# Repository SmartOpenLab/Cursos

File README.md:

# Cursos

Cursos impartidos por Smart Open Lab:

- Charla para laboratorios de la [Red Circular Fab](www.circular.es): *¿Qué se puede hacer en un fablab? Ejemplos desde SOL.*
  
- Curso de Arduino Básico: Entradas y salidas, Analógicas y Digitales y PWM
  
- Curso de Arduino Básico: Multi Sensor Shield

- Curso de Electrónica Básica: conceptos, dispositivos y circuitos fundamentales.
 
- Curso de Electrónica de Válvulas de Vacío para Guitarritas: Conceptos fundamentales, circuitos típicos, precauciones de seguridad...

- Curso de Freecad Básico: ejemplos de diseño y enlace a los videos del curso.

- Curso de diseño electrónico con Kicad de dos sesiones para la Red Circular Fab: ejemplos de diseño y enlace a los videos 3#.

 # Charlas

 Charlas impartidas por Smart Open Lab:
 
- Presentación de la charla impartida en "Fab17: Bali Fab Fest – Designing Emergent Realities" en Bali, Indonesia, octubre de 2022.
  
- Presentación del trabajo presentado en "FabFest 23 – Designing Relisient Futures" en Thimphu, Bután, julio de 2023.
  
- Presentación de la charla pronunciada en "FabFest 23 – Designing Relisient Futures" en Thimphu, Bután, julio de 2023.

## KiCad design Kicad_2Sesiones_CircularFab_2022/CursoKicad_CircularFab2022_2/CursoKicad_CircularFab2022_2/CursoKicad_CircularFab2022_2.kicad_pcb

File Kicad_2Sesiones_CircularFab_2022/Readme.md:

Curso de diseño electrónico con Kicad
=======

Aprende Kicad en dos sesiones online: del esquema a la PCB.

Impartidos desde el fablab [Smart Open Lab](www.smartopenlab.com), dentro del ciclo de cursos de 2022 para la dinamización de la [Red Circular Fab](https://circularfab.es/).

Contenidos
------------

**Primera sesión:** _Arrancando con Kicad_

* ¿Qué es diseño electrónico? Flujo de desarrollo de diseño.
* ¿Qué ofrece Kicad?
* ¡Manos a la obra!
* Iniciando un proyecto.
  * El editor de esquemas.
  * El editor de PCB.
  * El editor de Símbolos.
  * El editor de Huellas.

**Segunda sesión:** _Kicad intermedio_

* Campos extras en componentes.
* Añadiendo pads y agujeros.
* Añadiendo imágenes a la placa.
* Exportando modelos 3D a Freecad.
* Subiendo proyectos a webs de fabricantes (Aisler).
* Simulaciones de circuitos con Spice (link y link).

**Materiales incluídos:**
* Presentación del curso (breve).
* Enlaces a videos de youtube:
  * [Primera Sesión](https://www.youtube.com/watch?v=K_PexNjK7Dc&t=83s).
  * [Segunda Sesión](https://www.youtube.com/watch?v=kZ3RvHSpxto).
* Ficheros de diseño de los circuitos de cada sesión.
* Modelo de SPICE del transistor BC546.

**Profesor:**

[Antonio Gordillo Guerrero ](https://www.linkedin.com/in/antonio-gordillo-guerrero-8b820b88/?originalSubdomain=es) (anto@unex.es)

Departamento de Ingeniería Eléctrica Electrónica y Automática.

[Escuela Politécnica](https://www.unex.es/conoce-la-uex/centros/epcc), [Universidad de Extremadura](https://www.unex.es). España.

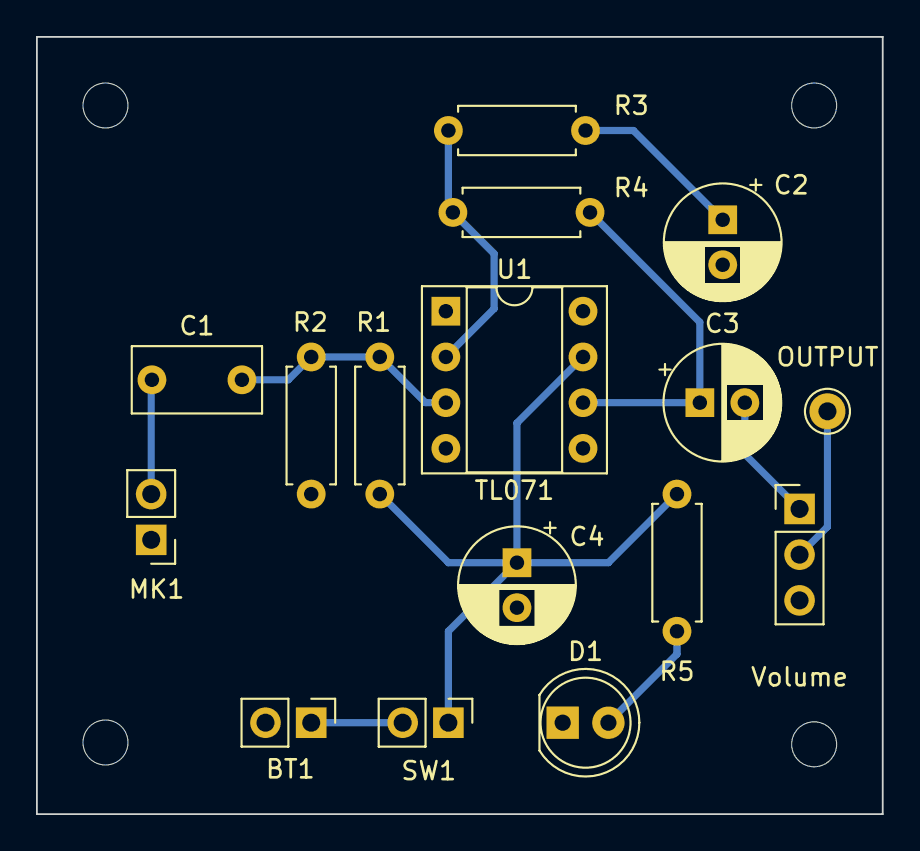
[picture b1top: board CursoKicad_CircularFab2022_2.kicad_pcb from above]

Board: 2 copper layers, 47.0 x 43.2 mm, 20 parts (0 on the bottom side), 11 nets.

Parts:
BT1: 9V; PinHeader_1x02_P2.54mm_Vertical
C1: C; C_Rect_L7.0mm_W3.5mm_P5.00mm
C2: C_Polarized; CP_Radial_D6.3mm_P2.50mm
C3, C4: 10u; CP_Radial_D6.3mm_P2.50mm
D1: Red; LED_D5.0mm
H1, H2, H3, H4: MountingHole; MountingHole_2.5mm
J1: Conn_01x01_Female; Pin_D1.0mm_L10.0mm
MK1: Piezoelectric_cell; PinHeader_1x02_P2.54mm_Vertical
R1, R2: 2M2; R_Axial_DIN0207_L6.3mm_D2.5mm_P7.62mm_Horizontal
R3: 100k; R_Axial_DIN0207_L6.3mm_D2.5mm_P7.62mm_Horizontal
R4: 220k; R_Axial_DIN0207_L6.3mm_D2.5mm_P7.62mm_Horizontal
R5: 1k; R_Axial_DIN0207_L6.3mm_D2.5mm_P7.62mm_Horizontal
RV1: R_Potentiometer; PinHeader_1x03_P2.54mm_Vertical
SW1: Switch_SPST; PinHeader_1x02_P2.54mm_Vertical
U1: TL071; DIP-8_W7.62mm_Socket

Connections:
GND: BT1.2 (-), C2.2, C4.2, D1.1 (K), MK1.1 (-), R2.2, RV1.3, U1.4 (V-)
unnamed: BT1.1 (+), SW1.2 (B)
unnamed: C1.1, MK1.2 (+)
unnamed: C1.2, R1.2, R2.1, U1.3 (+)
unnamed: C2.1, R3.2
unnamed: C3.1, R4.2, U1.6
unnamed: C3.2, RV1.1
unnamed: C4.1, R1.1, R5.2, SW1.1 (A), U1.7 (V+)
unnamed: D1.2 (A), R5.1
unnamed: J1.1, RV1.2
unnamed: R3.1, R4.1, U1.2 (-)

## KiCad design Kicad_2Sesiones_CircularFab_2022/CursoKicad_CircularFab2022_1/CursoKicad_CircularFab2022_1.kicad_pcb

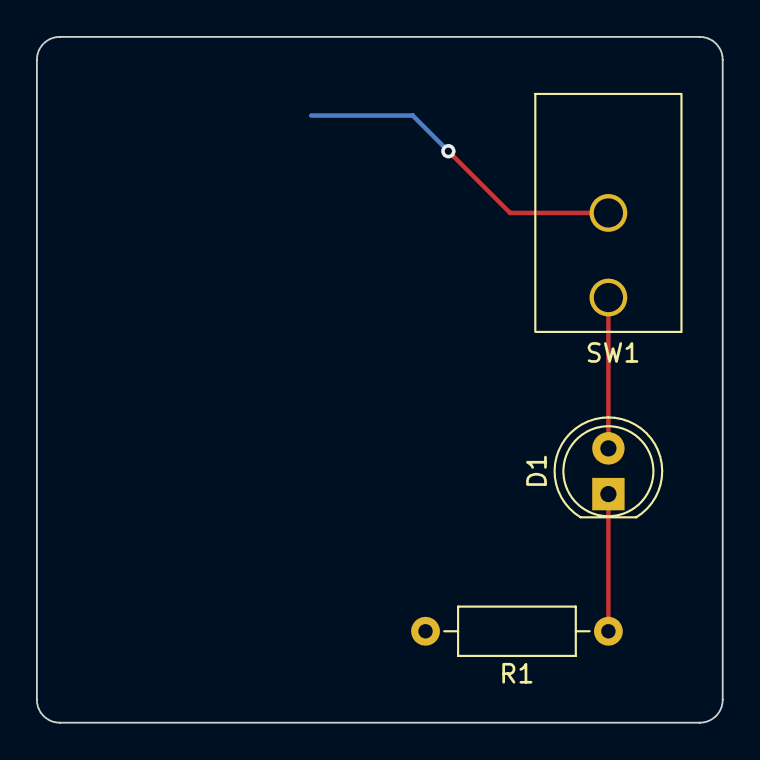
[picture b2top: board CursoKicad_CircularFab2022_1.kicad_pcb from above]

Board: 2 copper layers, 38.1 x 38.1 mm, 4 parts (1 on the bottom side), 4 nets.

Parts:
BT1: 3V3; BatteryHolder_Keystone_1058_1x2032
D1: rojo; LED_D5.0mm
R1: 1k; R_Axial_DIN0207_L6.3mm_D2.5mm_P10.16mm_Horizontal
SW1: SPST; Switch_Toogle_SPST_NKK_M2011S3Ax03

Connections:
GND: BT1.2 (-), R1.2
unnamed: D1.1 (K), R1.1
unnamed: D1.2 (A), SW1.3 (B)
VCC: BT1.1 (+), SW1.2 (A)

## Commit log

2016-12-21 Añadido Curso de Arduino Basico de @joriks y @mariesalguerog
2017-01-25 Update Arduino Course
2018-04-07 Added new course for arduino day
2020-12-03 Removed submodule of arduino course
2020-12-03 Skecth del control de un servo por medio de un joystick y diagrama de montaje
    Utilización de los conocimientos adquiridos en los anteriores montajes para la ampliación de un sistema
2020-12-03 Skecth de un semaforo con leds y diagrama de montaje
    semaforo de coches y peatones
    imagenes de los dispositivos generales utilizados
2020-12-03 Skecth del control de un joystick y diagrama de montaje
    uso de un pin analógico para la lectura del joystick
2020-12-03 Skecth del control de un servo de 180º y diagrama de montaje
    Uso de la librería servo.h para el control del servomotor
2020-12-03 Skecth de led y diagrama de montaje
    uso de un pin digital para hacer parpadear un led.
2020-12-03 Skecth del control de un sensor de ultrasonido y diagrama de montaje
    Uso de las funciones delayMicrosecond y pulseIn para la detección del echo del sensor
2020-12-03 Actualizado readme.md y agregados ficheros de diagramas
2020-12-03 Actualizado readme.md
2020-12-03 Skecths actualizados a los ejercicios del curso/taller
    Skecth Joystick, Servo, ultrasonido y Joystick con servo actualizados a la nueva revisión del taller
2020-12-03 Modificado readme's y esquemas
    Modificacion en los readme (uno para cada ejercicio y la introduccion), añadidos esquemas de cada ejercicio con nombres nuevos y .ino
2020-12-03 Añadido acceso a imagenes en readme's
    Añadido acceso a imagenes en readme's y cambiado nombre de un esquema por problemas con parentesis
    Cambiado el archivo readme del ejercicio4 que estaba mal
2020-12-03 Cambiadas y añadidas imagenes
    Cambiados los textos para que aparezcan bien las imagenes y la redaccion para que se lea mejor.
    Añadidas imagenes de algunos montajes.
2020-12-03 Cambios de redaccion olvidados
    Cambios en readme de introduccion olvidados
2020-12-03 Added course basic arduino from remote repo
2020-12-03 Updated without local history
